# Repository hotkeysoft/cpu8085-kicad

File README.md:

# 8085 Computer
Rev B September 2018

Based on original 2001 design

Features
============
- 32KB ROM 
  - Address [0x0000-7FFF]
- 32KB RAM
  - Address [0x8000-FFFF]
- 82C54 PIT (Programmable Interval Timer) 
  - Port [0x40-0x43]
- UART 8250 or 16550 
  - Port [0x60-0x67]
  - Connected to FTDI Serial<->USB Adapter

Notes
============
- This board was never produced. The FT232RL circuit was prototyped so in works in theory. 
  For a known working version see [Rev A](https://github.com/hotkeysoft/cpu8085-kicad/tree/revA)
- No voltage regulation on board, no protection of any kind
- I made a somewhat working BASIC interpreter from scratch that runs on this hardware: [pfe_8085basic](https://github.com/hotkeysoft/pfe_8085basic)

Changes from [Rev A](https://github.com/hotkeysoft/cpu8085-kicad/tree/revA)
============
- Changed FTDI-USB module with FT232RL

Images
============
### PCB Render

### Schematics (pdf)
- [Complete schematics](./img/schema.pdf)

### PCB Images (svg)
- [Top](./img/pcb-front.svg)
- [Bottom](./img/pcb-back.svg)

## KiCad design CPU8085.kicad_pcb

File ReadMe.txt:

CPU8085 Rev A
September 2018 by Dominic Thibodeau

Based on original 2001 design

Notes
-----
- No voltage regulation on board, no protection of any kind

Changes from original design
----------------------------
- Changed crystal to 4MHz (CPU Freq = 2MHz)
	- Original design ran at 1.8432MHz (CPU Freq = 921.6KHz)

- Replaced MAX232 chip with FTDI USB module

- Replaced 2 PLA (address latch) with one 74HCT573 (for A[0..7] only, not needed for A[8..15])

- Instead of MISC (0x80) port and additional logic for gating the sound, used /OUT1 of 8250 UART
	- /OUT2 remains unused
	- Needed to invert /OUT2 signal to gate 82C54 timer, and to invert the sound output
		- 2 inverters added to DTGLUE3 (see below)

- Removed IO Decoding chip, moved /UART and /PIT decoding to DTGLUE3
	- Removed IO Decoding for keyboard and LCD

- Glue logic PLA (DTGLUE3) improvements from original DTGLUE1 (see PLD/DTGLUE3.PDS)
	- Removed /IOR, /IOW, /MR, /MW - not needed with properly constructed /CS signals and CPU /WR /RD
		- Added IO Decoding (/CS signal for /UART and /PIT)
	- Removed ALE, no need for inverted signal since switching to 74HCT573
	- Replaced A15 A7 A6 A5 (redundant because A15 == A7 for IO) with A15 A14 A13
		- On 8085, for IO Ports, port address is on both A[0..7] AND A[8..15]
	- 3 inputs and 3 outputs remain on PLA, for future use

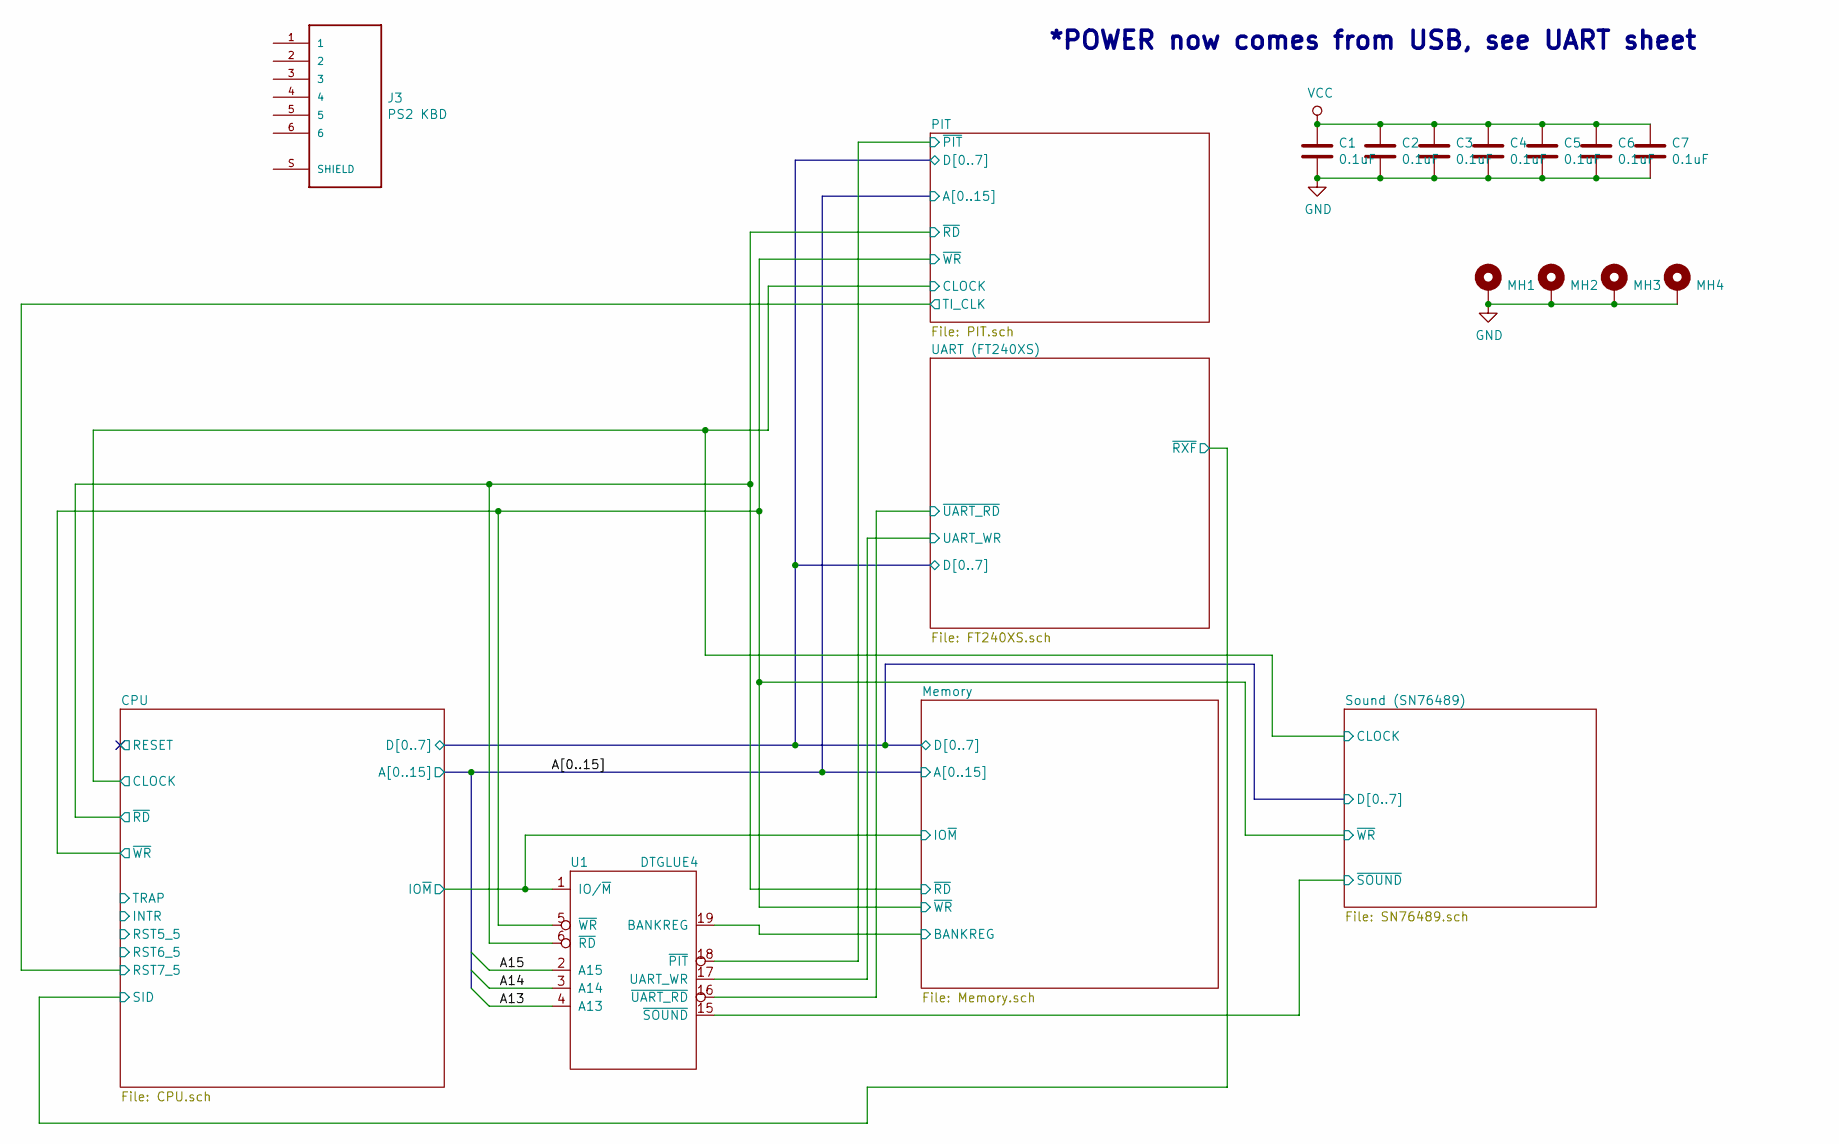
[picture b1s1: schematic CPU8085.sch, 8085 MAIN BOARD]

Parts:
C1, C2, C3, C4, C5, C6, C7: 0.1uF; C_0805_2012Metric_Pad1.15x1.40mm_HandSolder
J3: PS2 KBD; CUI_MD-60S
MH1, MH2, MH3, MH4: MountingHole_Pad; MountingHole_2.7mm_M2.5_Pad
U1: DTGLUE4; DIP-20_W7.62mm

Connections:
/A13: U1.4 (A13); also elsewhere on the board
/A14: U1.3 (A14); also elsewhere on the board
/A15: U1.2 (A15); also elsewhere on the board
/CPU/IO~M: U1.1 (IO/~M); also elsewhere on the board
/CPU/~RD: U1.6 (~RD); also elsewhere on the board
/CPU/~WR: U1.5 (~WR); also elsewhere on the board
/Memory/BANKREG: U1.19 (BANKREG); also elsewhere on the board
/PIT/~PIT: U1.18 (~PIT); also elsewhere on the board
/Sound (SN76489)/~SOUND: U1.15 (~SOUND); also elsewhere on the board
/UART (FT240XS)/UART_WR: U1.17 (UART_WR); also elsewhere on the board
/UART (FT240XS)/~UART_RD: U1.16 (~UART_RD); also elsewhere on the board
GND: C1.2, C2.2, C3.2, C4.2, C5.2, C6.2, C7.2, MH1.1, MH2.1, MH3.1, MH4.1, U1.10 (GND); also elsewhere on the board
VCC: C1.1, C2.1, C3.1, C4.1, C5.1, C6.1, C7.1, U1.20 (VCC); also elsewhere on the board

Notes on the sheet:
*POWER now comes from USB, see UART sheet

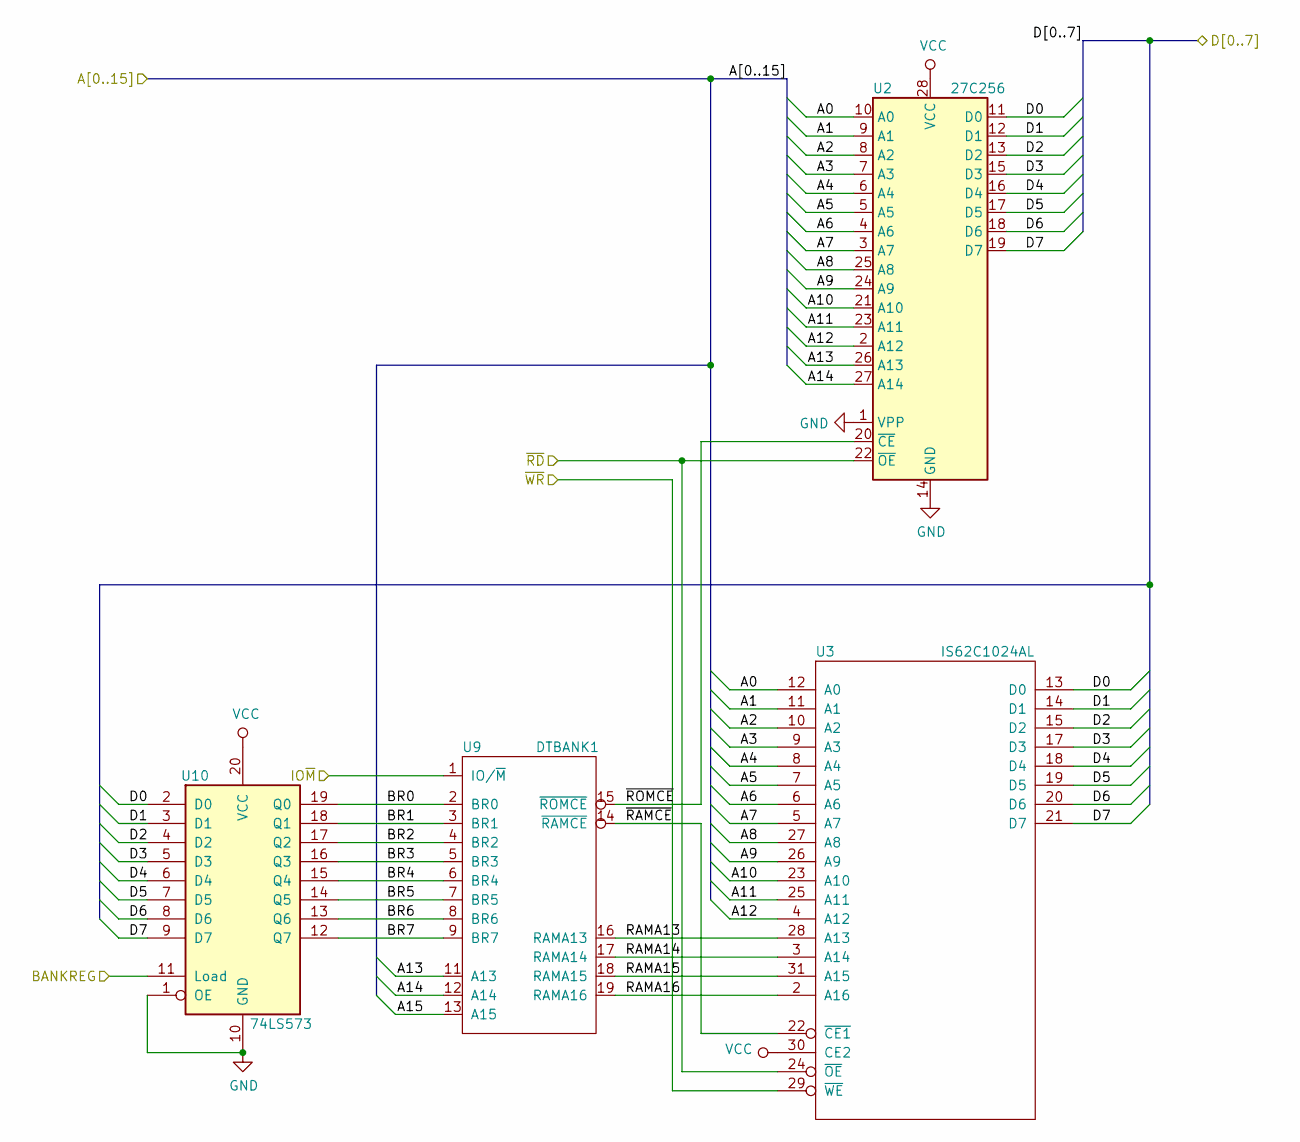
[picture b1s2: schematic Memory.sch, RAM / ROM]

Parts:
U2: 27C256; DIP-28_W15.24mm_Socket
U3: IS62C1024AL; SOIC-32W_14x21mm_P1.27mm
U9: DTBANK1; DIP-20_W7.62mm
U10: 74LS573; DIP-20_W7.62mm

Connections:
/A13: U2.26 (A13), U9.11 (A13); also elsewhere on the board
/A14: U2.27 (A14), U9.12 (A14); also elsewhere on the board
/A15: U9.13 (A15); also elsewhere on the board
/CPU/A0: U2.10 (A0), U3.12 (A0); also elsewhere on the board
/CPU/A1: U2.9 (A1), U3.11 (A1); also elsewhere on the board
/CPU/A2: U2.8 (A2), U3.10 (A2); also elsewhere on the board
/CPU/A3: U2.7 (A3), U3.9 (A3); also elsewhere on the board
/CPU/A4: U2.6 (A4), U3.8 (A4); also elsewhere on the board
/CPU/A5: U2.5 (A5), U3.7 (A5); also elsewhere on the board
/CPU/A6: U2.4 (A6), U3.6 (A6); also elsewhere on the board
/CPU/A7: U2.3 (A7), U3.5 (A7); also elsewhere on the board
/CPU/A8: U2.25 (A8), U3.27 (A8); also elsewhere on the board
/CPU/A9: U2.24 (A9), U3.26 (A9); also elsewhere on the board
/CPU/A10: U2.21 (A10), U3.23 (A10); also elsewhere on the board
/CPU/A11: U2.23 (A11), U3.25 (A11); also elsewhere on the board
/CPU/A12: U2.2 (A12), U3.4 (A12); also elsewhere on the board
/CPU/D0: U2.11 (D0), U3.13 (D0), U10.2 (D0); also elsewhere on the board
/CPU/D1: U2.12 (D1), U3.14 (D1), U10.3 (D1); also elsewhere on the board
/CPU/D2: U2.13 (D2), U3.15 (D2), U10.4 (D2); also elsewhere on the board
/CPU/D3: U2.15 (D3), U3.17 (D3), U10.5 (D3); also elsewhere on the board
/CPU/D4: U2.16 (D4), U3.18 (D4), U10.6 (D4); also elsewhere on the board
/CPU/D5: U2.17 (D5), U3.19 (D5), U10.7 (D5); also elsewhere on the board
/CPU/D6: U2.18 (D6), U3.20 (D6), U10.8 (D6); also elsewhere on the board
/CPU/D7: U2.19 (D7), U3.21 (D7), U10.9 (D7); also elsewhere on the board
/CPU/IO~M: U9.1 (IO/~M); also elsewhere on the board
/CPU/~RD: U2.22 (~OE), U3.24 (~OE); also elsewhere on the board
/CPU/~WR: U3.29 (~WE); also elsewhere on the board
/Memory/BANKREG: U10.11 (Load); also elsewhere on the board
/Memory/BR0: U9.2 (BR0), U10.19 (Q0)
/Memory/BR1: U9.3 (BR1), U10.18 (Q1)
/Memory/BR2: U9.4 (BR2), U10.17 (Q2)
/Memory/BR3: U9.5 (BR3), U10.16 (Q3)
/Memory/BR4: U9.6 (BR4), U10.15 (Q4)
/Memory/BR5: U9.7 (BR5), U10.14 (Q5)
/Memory/BR6: U9.8 (BR6), U10.13 (Q6)
/Memory/BR7: U9.9 (BR7), U10.12 (Q7)
/Memory/RAMA13: U3.28 (A13), U9.16 (RAMA13)
/Memory/RAMA14: U3.3 (A14), U9.17 (RAMA14)
/Memory/RAMA15: U3.31 (A15), U9.18 (RAMA15)
/Memory/RAMA16: U3.2 (A16), U9.19 (RAMA16)
/Memory/~RAMCE: U3.22 (~CE1), U9.14 (~RAMCE)
/Memory/~ROMCE: U2.20 (~CE), U9.15 (~ROMCE)
GND: U2.1 (VPP), U2.14 (GND), U3.16 (GND), U9.10 (GND), U10.1 (OE), U10.10 (GND); also elsewhere on the board
VCC: U2.28 (VCC), U3.30 (CE2), U3.32 (VCC), U9.20 (VCC), U10.20 (VCC); also elsewhere on the board

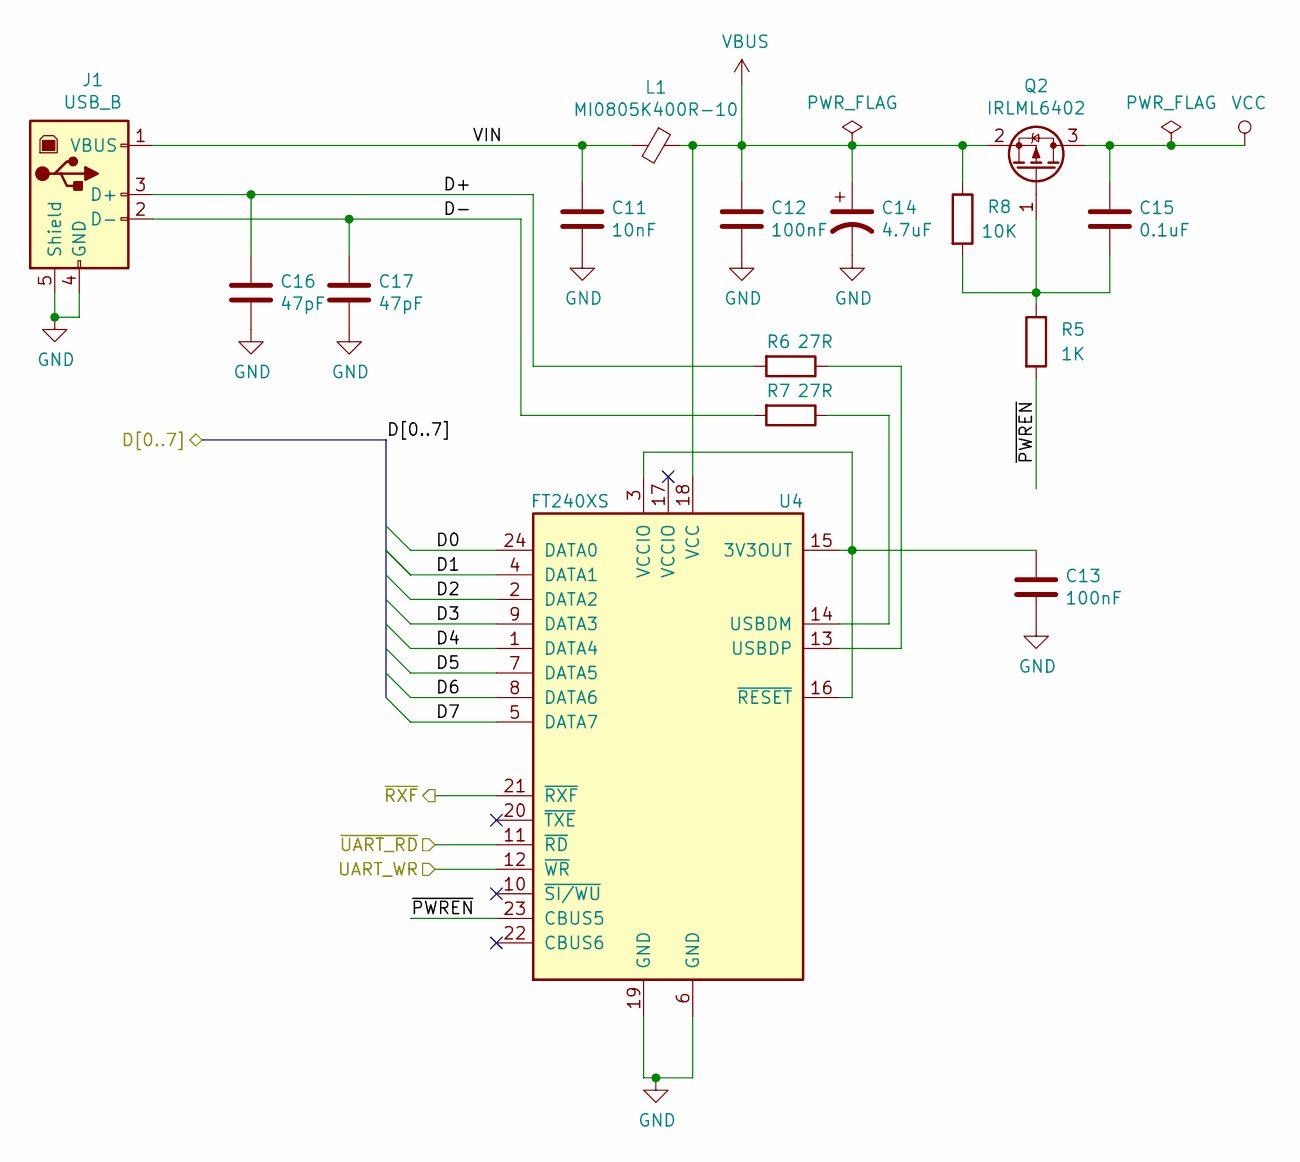
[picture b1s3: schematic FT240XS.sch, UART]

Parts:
C11: 10nF; C_0805_2012Metric_Pad1.15x1.40mm_HandSolder
C12, C13: 100nF; C_0805_2012Metric_Pad1.15x1.40mm_HandSolder
C14: 4.7uF; CP_Radial_D5.0mm_P2.50mm
C15: 0.1uF; C_0805_2012Metric_Pad1.15x1.40mm_HandSolder
C16, C17: 47pF; C_0805_2012Metric_Pad1.15x1.40mm_HandSolder
J1: USB_B; USB_B_OST_USB-B1HSxx_Horizontal
L1: MI0805K400R-10; L_0805_2012Metric_Pad1.15x1.40mm_HandSolder
Q2: IRLML6402; SOT-23
R5: 1K; R_0805_2012Metric_Pad1.15x1.40mm_HandSolder
R6, R7: 27R; R_0805_2012Metric_Pad1.15x1.40mm_HandSolder
R8: 10K; R_0805_2012Metric_Pad1.15x1.40mm_HandSolder
U4: FT240XS; SSOP-24_3.9x8.7mm_P0.635mm

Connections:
/CPU/D0: U4.24 (DATA0); also elsewhere on the board
/CPU/D1: U4.4 (DATA1); also elsewhere on the board
/CPU/D2: U4.2 (DATA2); also elsewhere on the board
/CPU/D3: U4.9 (DATA3); also elsewhere on the board
/CPU/D4: U4.1 (DATA4); also elsewhere on the board
/CPU/D5: U4.7 (DATA5); also elsewhere on the board
/CPU/D6: U4.8 (DATA6); also elsewhere on the board
/CPU/D7: U4.5 (DATA7); also elsewhere on the board
/CPU/SID: U4.21 (~RXF); also elsewhere on the board
/UART (FT240XS)/D+: C16.1, J1.3 (D+), R6.2
/UART (FT240XS)/D-: C17.1, J1.2 (D-), R7.2
/UART (FT240XS)/UART_WR: U4.12 (~WR); also elsewhere on the board
/UART (FT240XS)/VIN: C11.1, J1.1 (VBUS), L1.2
/UART (FT240XS)/~PWREN: R5.2, U4.23 (CBUS5)
/UART (FT240XS)/~UART_RD: U4.11 (~RD); also elsewhere on the board
GND: C11.2, C12.2, C13.2, C14.2, C16.2, C17.2, J1.4 (GND), J1.5 (Shield), U4.6 (GND), U4.19 (GND); also elsewhere on the board
unnamed: C13.1, U4.3 (VCCIO), U4.15 (3V3OUT), U4.16 (~RESET)
unnamed: C15.2, Q2.1 (G), R5.1, R8.2
unnamed: R6.1, U4.13 (USBDP)
unnamed: R7.1, U4.14 (USBDM)
VBUS: C12.1, C14.1, L1.1, Q2.2 (S), R8.1, U4.18 (VCC)
VCC: C15.1, Q2.3 (D); also elsewhere on the board

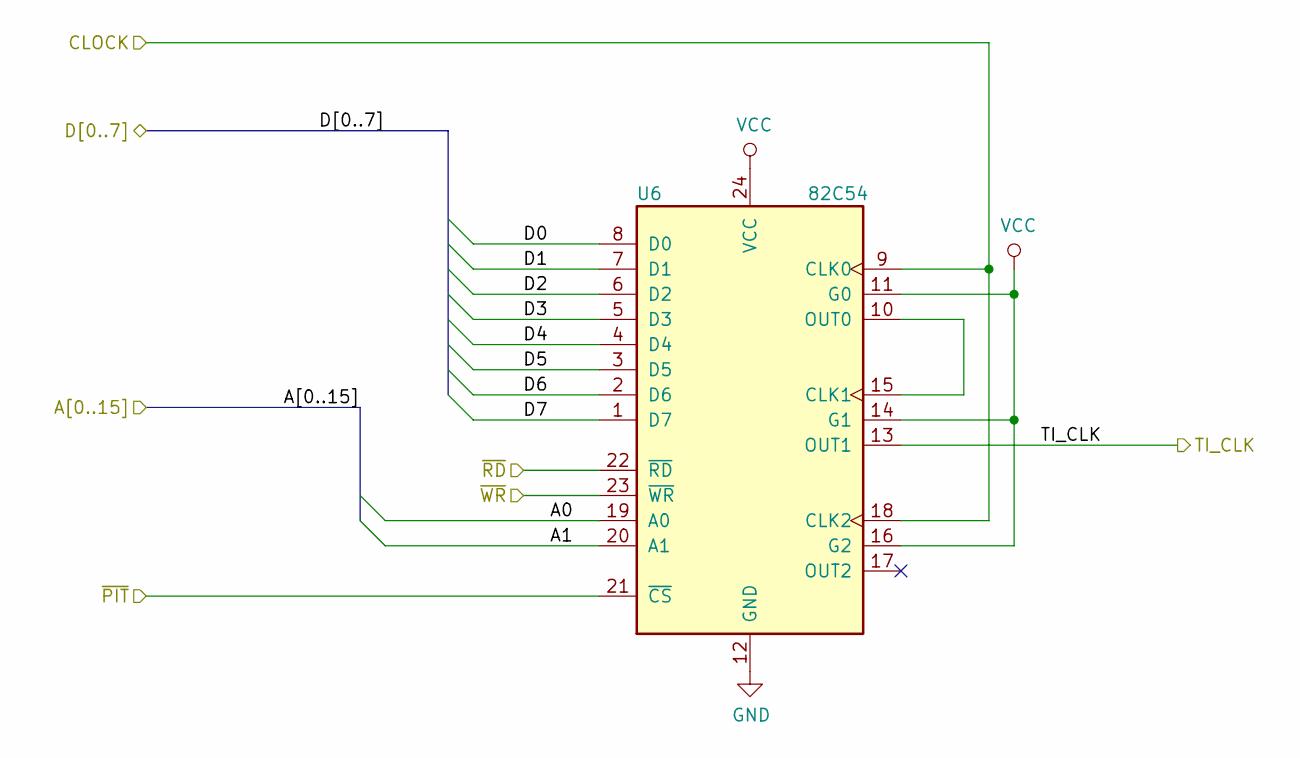
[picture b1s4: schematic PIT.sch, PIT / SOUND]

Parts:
U6: 82C54; DIP-24_W15.24mm_Socket

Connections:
/CPU/A0: U6.19 (A0); also elsewhere on the board
/CPU/A1: U6.20 (A1); also elsewhere on the board
/CPU/CLOCK: U6.9 (CLK0), U6.18 (CLK2); also elsewhere on the board
/CPU/D0: U6.8 (D0); also elsewhere on the board
/CPU/D1: U6.7 (D1); also elsewhere on the board
/CPU/D2: U6.6 (D2); also elsewhere on the board
/CPU/D3: U6.5 (D3); also elsewhere on the board
/CPU/D4: U6.4 (D4); also elsewhere on the board
/CPU/D5: U6.3 (D5); also elsewhere on the board
/CPU/D6: U6.2 (D6); also elsewhere on the board
/CPU/D7: U6.1 (D7); also elsewhere on the board
/CPU/RST7_5: U6.13 (OUT1); also elsewhere on the board
/CPU/~RD: U6.22 (~RD~); also elsewhere on the board
/CPU/~WR: U6.23 (~WR~); also elsewhere on the board
/PIT/~PIT: U6.21 (~CS~); also elsewhere on the board
GND: U6.12 (GND); also elsewhere on the board
unnamed: U6.10 (OUT0), U6.15 (CLK1)
VCC: U6.11 (G0), U6.14 (G1), U6.16 (G2), U6.24 (VCC); also elsewhere on the board

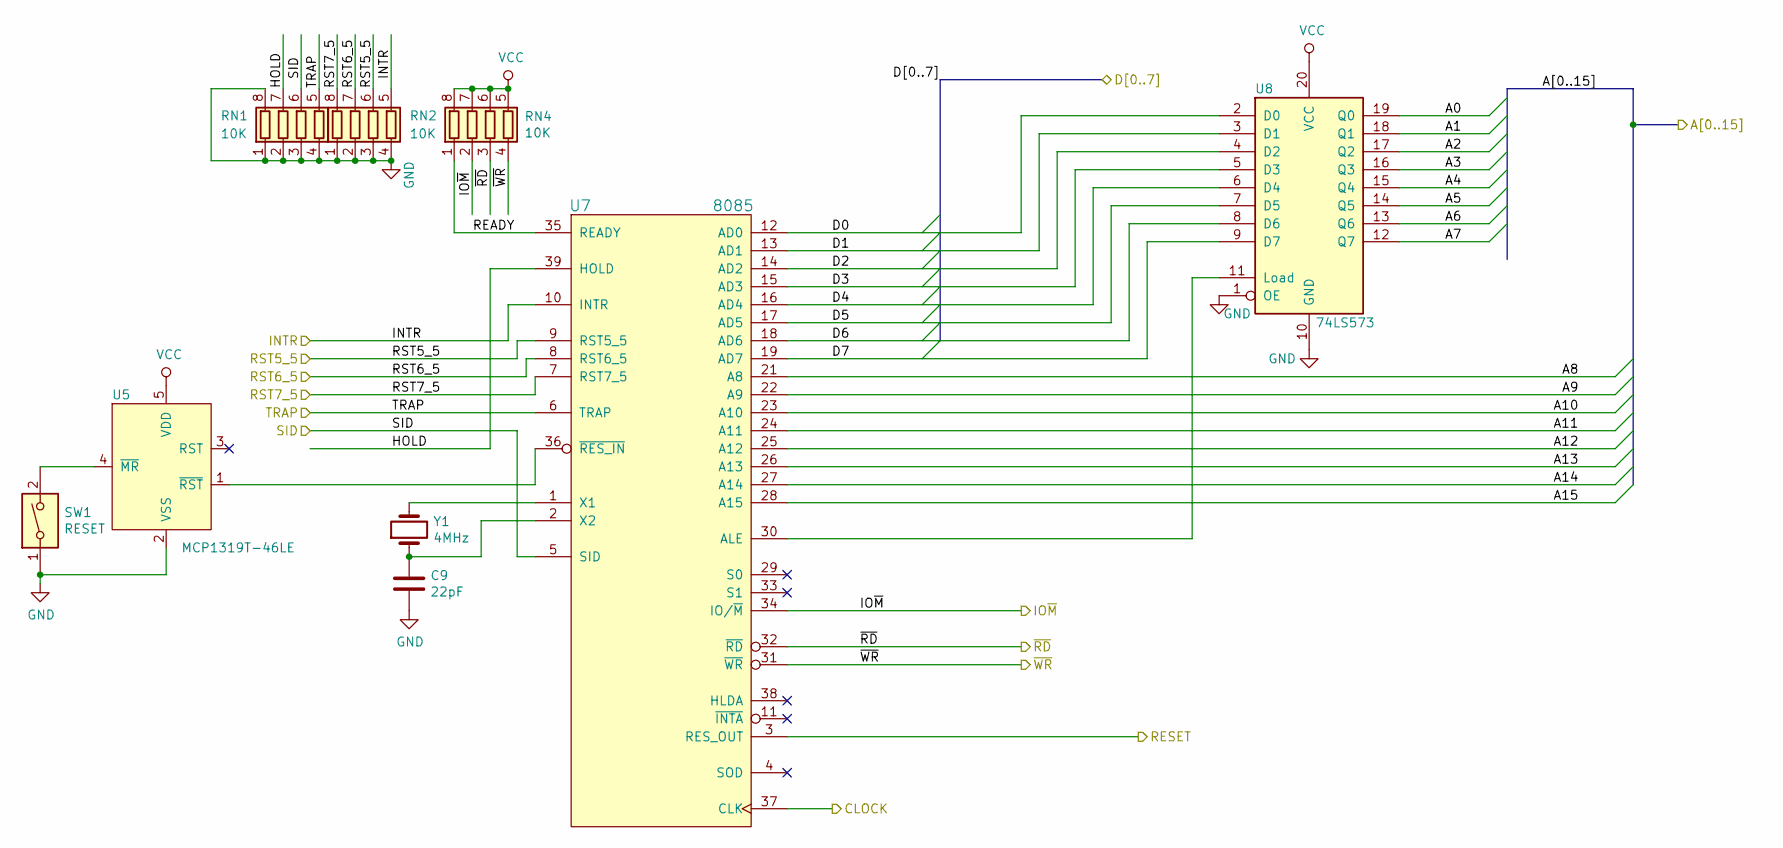
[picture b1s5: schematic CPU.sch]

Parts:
C9: 22pF; C_Disc_D3.0mm_W1.6mm_P2.50mm
RN1, RN2, RN4: 10K; R_Array_Convex_4x1206
SW1: RESET; Switch_Tactile_SMD_6x6mm_PTS645
U5: MCP1319T-46LE; SOT-23-5_HandSoldering
U7: 8085; DIP-40_W15.24mm_Socket
U8: 74LS573; DIP-20_W7.62mm
Y1: 4MHz; Crystal_HC49-U_Vertical

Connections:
/A13: U7.26 (A13); also elsewhere on the board
/A14: U7.27 (A14); also elsewhere on the board
/A15: U7.28 (A15); also elsewhere on the board
/CPU/A0: U8.19 (Q0); also elsewhere on the board
/CPU/A1: U8.18 (Q1); also elsewhere on the board
/CPU/A2: U8.17 (Q2); also elsewhere on the board
/CPU/A3: U8.16 (Q3); also elsewhere on the board
/CPU/A4: U8.15 (Q4); also elsewhere on the board
/CPU/A5: U8.14 (Q5); also elsewhere on the board
/CPU/A6: U8.13 (Q6); also elsewhere on the board
/CPU/A7: U8.12 (Q7); also elsewhere on the board
/CPU/A8: U7.21 (A8); also elsewhere on the board
/CPU/A9: U7.22 (A9); also elsewhere on the board
/CPU/A10: U7.23 (A10); also elsewhere on the board
/CPU/A11: U7.24 (A11); also elsewhere on the board
/CPU/A12: U7.25 (A12); also elsewhere on the board
/CPU/CLOCK: U7.37 (CLK); also elsewhere on the board
/CPU/D0: U7.12 (AD0), U8.2 (D0); also elsewhere on the board
/CPU/D1: U7.13 (AD1), U8.3 (D1); also elsewhere on the board
/CPU/D2: U7.14 (AD2), U8.4 (D2); also elsewhere on the board
/CPU/D3: U7.15 (AD3), U8.5 (D3); also elsewhere on the board
/CPU/D4: U7.16 (AD4), U8.6 (D4); also elsewhere on the board
/CPU/D5: U7.17 (AD5), U8.7 (D5); also elsewhere on the board
/CPU/D6: U7.18 (AD6), U8.8 (D6); also elsewhere on the board
/CPU/D7: U7.19 (AD7), U8.9 (D7); also elsewhere on the board
/CPU/HOLD: RN1.7 (R2.2), U7.39 (HOLD)
/CPU/INTR: RN2.5 (R4.2), U7.10 (INTR)
/CPU/IO~M: RN4.2 (R2.1), U7.34 (IO/~M); also elsewhere on the board
/CPU/READY: RN4.1 (R1.1), U7.35 (READY)
/CPU/RESET: U7.3 (RES_OUT)
/CPU/RST5_5: RN2.6 (R3.2), U7.9 (RST5_5)
/CPU/RST6_5: RN2.7 (R2.2), U7.8 (RST6_5)
/CPU/RST7_5: RN2.8 (R1.2), U7.7 (RST7_5); also elsewhere on the board
/CPU/SID: RN1.6 (R3.2), U7.5 (SID); also elsewhere on the board
/CPU/TRAP: RN1.5 (R4.2), U7.6 (TRAP)
/CPU/~RD: RN4.3 (R3.1), U7.32 (~RD); also elsewhere on the board
/CPU/~WR: RN4.4 (R4.1), U7.31 (~WR); also elsewhere on the board
GND: C9.2, RN1.1 (R1.1), RN1.2 (R2.1), RN1.3 (R3.1), RN1.4 (R4.1), RN1.8 (R1.2), RN2.1 (R1.1), RN2.2 (R2.1), RN2.3 (R3.1), RN2.4 (R4.1), SW1.1, U5.2 (VSS), U7.20 (GND), U8.1 (OE), U8.10 (GND); also elsewhere on the board
unnamed: C9.1, U7.2 (X2), Y1.1
unnamed: SW1.2, U5.4 (~MR)
unnamed: U5.1 (~RST), U7.36 (~RES_IN)
unnamed: U7.1 (X1), Y1.2
unnamed: U7.30 (ALE), U8.11 (Load)
VCC: RN4.5 (R4.2), RN4.6 (R3.2), RN4.7 (R2.2), RN4.8 (R1.2), U5.5 (VDD), U7.40 (VCC), U8.20 (VCC); also elsewhere on the board

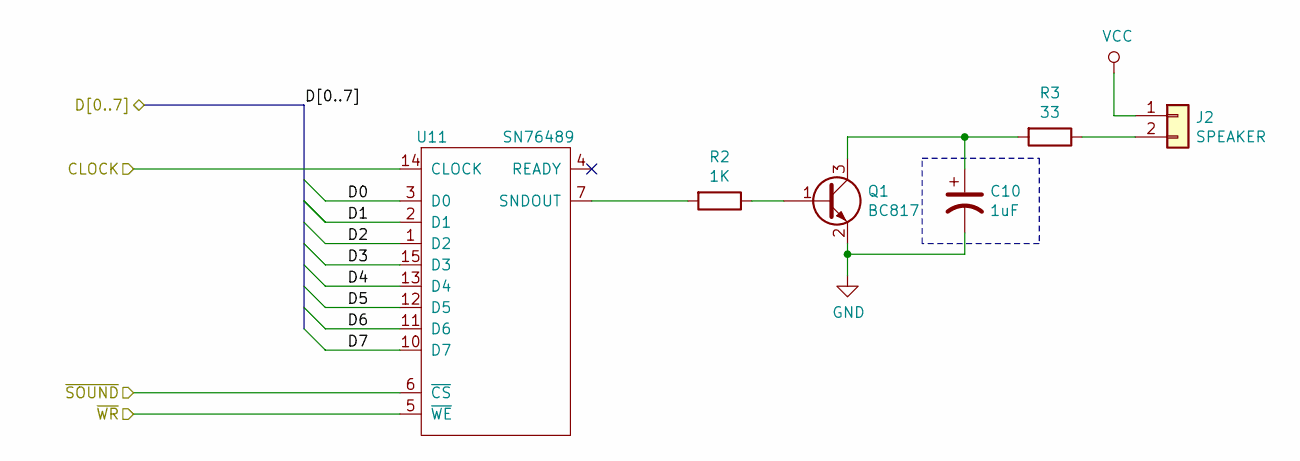
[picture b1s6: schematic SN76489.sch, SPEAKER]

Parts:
C10: 1uF; CP_Radial_D5.0mm_P2.50mm
J2: SPEAKER; PinHeader_1x02_P2.54mm_Vertical
Q1: BC817; SOT-23
R2: 1K; R_Axial_DIN0207_L6.3mm_D2.5mm_P10.16mm_Horizontal
R3: 33; R_Axial_DIN0207_L6.3mm_D2.5mm_P10.16mm_Horizontal
U11: SN76489; DIP-16_W7.62mm_Socket

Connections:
/CPU/CLOCK: U11.14 (CLOCK); also elsewhere on the board
/CPU/D0: U11.3 (D0); also elsewhere on the board
/CPU/D1: U11.2 (D1); also elsewhere on the board
/CPU/D2: U11.1 (D2); also elsewhere on the board
/CPU/D3: U11.15 (D3); also elsewhere on the board
/CPU/D4: U11.13 (D4); also elsewhere on the board
/CPU/D5: U11.12 (D5); also elsewhere on the board
/CPU/D6: U11.11 (D6); also elsewhere on the board
/CPU/D7: U11.10 (D7); also elsewhere on the board
/CPU/~WR: U11.5 (~WE); also elsewhere on the board
/Sound (SN76489)/~SOUND: U11.6 (~CS); also elsewhere on the board
GND: C10.2, Q1.2 (E), U11.8 (GND); also elsewhere on the board
unnamed: C10.1, Q1.3 (C), R3.2
unnamed: J2.2, R3.1
unnamed: Q1.1 (B), R2.1
unnamed: R2.2, U11.7 (SNDOUT)
VCC: J2.1, U11.16 (VCC); also elsewhere on the board

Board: 2 copper layers, 48 parts (11 on the bottom side), 76 nets, no tracks yet.

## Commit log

2018-09-19 Moved to RevA
2018-09-19 Added ReadMe.txt
2018-10-16 Added bom
2020-07-02 Added images, .gitignore
2020-07-02 Fixed footprint for FTDI adapter
2020-07-02 Updated images
2020-07-02 RevB
2020-07-03 RevC
